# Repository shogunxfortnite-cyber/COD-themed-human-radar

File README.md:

# COD-themed-human-radar

## What is it
So basically its a,

radar with a LD2410C which can detect humans from a 6m range even when they are still, as the module also detects micromovements.

It also has a 2.8 inch TFT for displaying the fancy ui for the COD themed radar.

Its equipped with a ESP32 S3 DEVKIT C1 N16R8 for delivering fast and powerful performance.

## BOM

| Item | Qty | Supplier | Cost/item | Total Cost | Link |
| :--- | :---: | :--- | :---: | :---: | :--- |
| ESP32 S3 | 1 | Robocraze | $10.00 | $10.00 | [Link](https://robocraze.com/products/7semi-esp32-s3-dev-boardc-1-n8r8-wifi-bluetooth-dual-usb-c-rgb-led?variant=48519036272864) |
| 2.8 inch TFT | 1 | Robu | $7.00 | $7.00 | [Link](https://robu.in/product/2-8-inch-tft-lcd-non-touch-display-modulesd-card-support/) |
| The LD2410C | 1 | Robu | $7.00 | $7.00 | [Link](https://robu.in/product/hi-link-hlk-ld2410c-p-smd22x16mm-sensor-modules-rohs/) |
| The enclosure CAD | 1 | Robu | $4.00 | $4.00 | [Link](https://robu.in/product/3d-printing-service1/) |
| The PCB | 5 | Robu | $1.80 | $9.00 | [Link](https://robu.in/product/online-pcb-manufacturing-service/) |
| CAD lid | 1 | Robu | $2.00 | $2.00 | [Link](https://robu.in/product/3d-printing-service1/) |
| Estimated total shipping | 1 | - | $4.00 | $4.00 | - |
| **Total** | **11** | | | **$43.00** | |

# Guide
###### This course will guide you for making the PROJECT.

## Kicad

### Schematic 
So the schematic looks like this:

You can do the connections according to this.
#### Symbols and footprints 
For the symbols and footprints you can check out the folder named Symbols and footprints (It has already been made its just a copy), execept for esp 32, it can be natively downloaded from kicad itself.

### Footprint assignment

So you can assign the footprints according to  this image:

### PCB
So the initial start is like this:

Now we need to arrange it in a user friendly manner, so either you can arrange it like this or any other way which suites you:

Now comes the easy part, drawing the pcb outlines, this we would need to switch our current layer to edge.cuts and draw our custom outline.

I drew it like this:

Now comes the fun part routing, this has no restrictions, you can route it any way you want.

I have routed it like this:

For the red traces switch to F.cu layer and press X on your keyboard and for blue switch to B.cu.

Now comes the really fun part drawings, you can customize your board drawings your way.

Like this:

For the drawing part you would need to switch over to F.silkscreen.

### CAD 

For this part you have no restrictions, you can use any modelling software like freeCAD or tinkercad.

For making things easier you can import the radar.step and build the enclosure on top of it.

I made mine like this:

The Body:

The lid:

### Code 

For the code we would be using Arduino ide.

We can simply just copy and paste the code into arduino ide, set the board to esp32 s3 dev module and upload.

### final 3d view for PCB

## Problems I faced

I mainly faced problems in the CAD part as it was my first time designing an  enclosure for a PCB. The main problem was lifting the pcb up from the cad, so that the soldered pins dont clash with the CAD. It took me a time to figure it out but then I succeeded. With that I learnt how to design an enclosure in CAD.

# Built for half life

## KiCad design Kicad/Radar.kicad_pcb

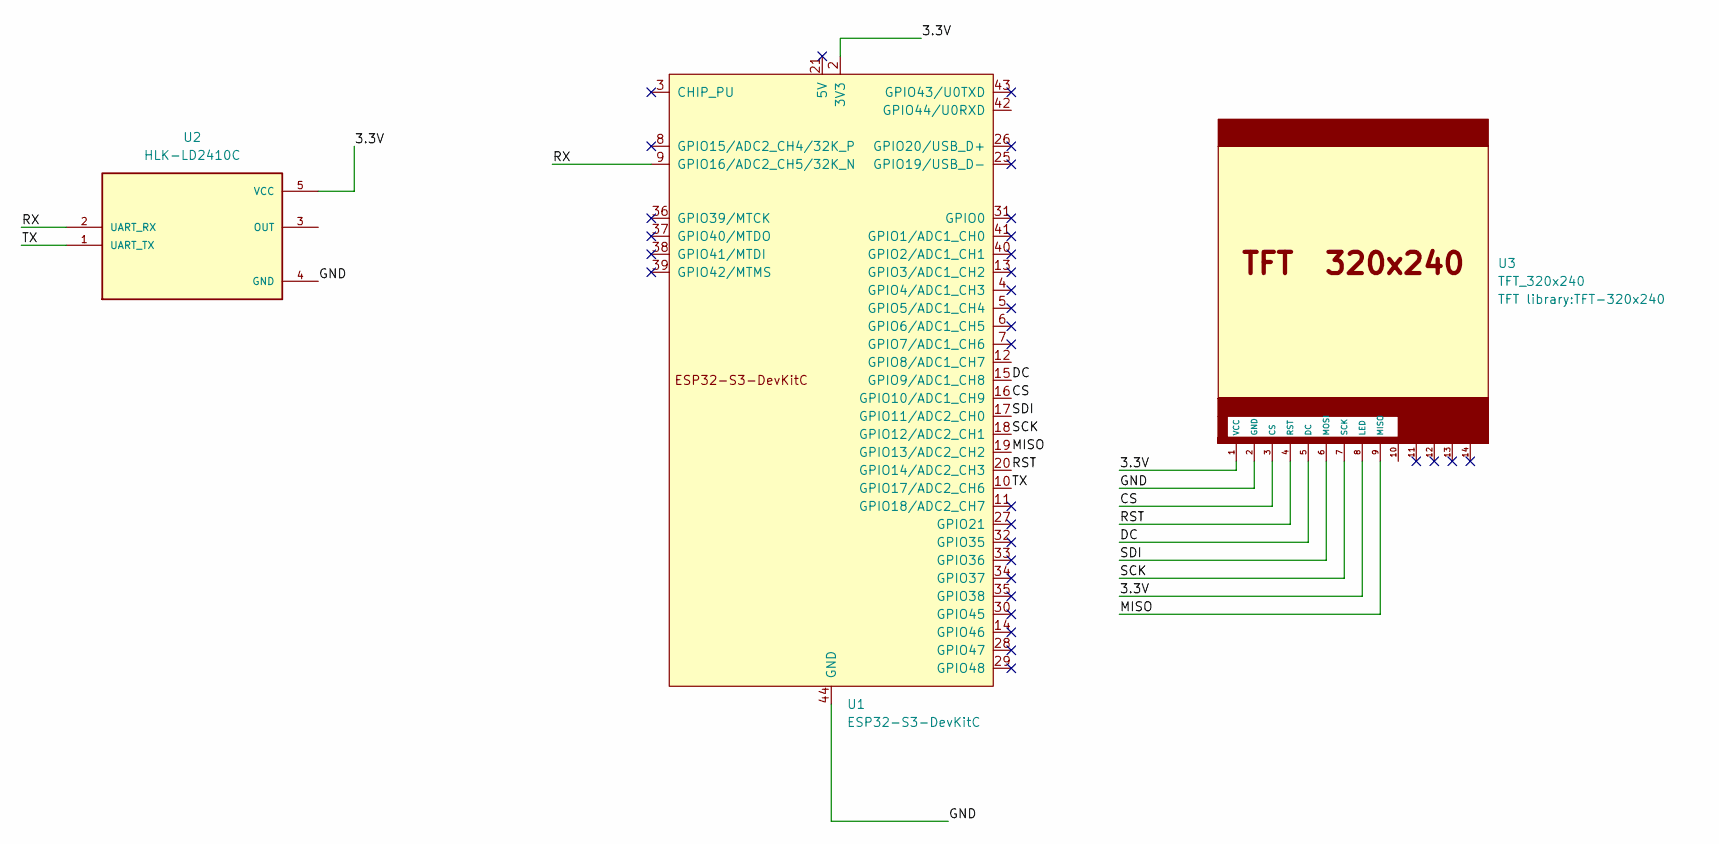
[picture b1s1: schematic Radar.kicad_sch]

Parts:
U1: ESP32-S3-DevKitC
U2: HLK-LD2410C; MODULE_HLK-LD2410C; PARTREV V1.00
U3: TFT_320x240; TFT-320x240

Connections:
/3.3V: U1.1 (3V3), U1.2 (3V3), U2.5 (VCC), U3.1 (VCC), U3.8 (LED)
/CS: U1.16 (GPIO10/ADC1_CH9), U3.3 (CS)
/DC: U1.15 (GPIO9/ADC1_CH8), U3.5 (DC)
/GND: U1.22 (GND), U1.23 (GND), U1.24 (GND), U1.44 (GND), U2.4 (GND), U3.2 (GND)
/MISO: U1.19 (GPIO13/ADC2_CH2), U3.9 (MISO)
/RST: U1.20 (GPIO14/ADC2_CH3), U3.4 (RST)
/RX: U1.9 (GPIO16/ADC2_CH5/32K_N), U2.2 (UART_RX)
/SCK: U1.18 (GPIO12/ADC2_CH1), U3.7 (SCK)
/SDI: U1.17 (GPIO11/ADC2_CH0), U3.6 (MOSI)
/TX: U1.10 (GPIO17/ADC2_CH6), U2.1 (UART_TX)

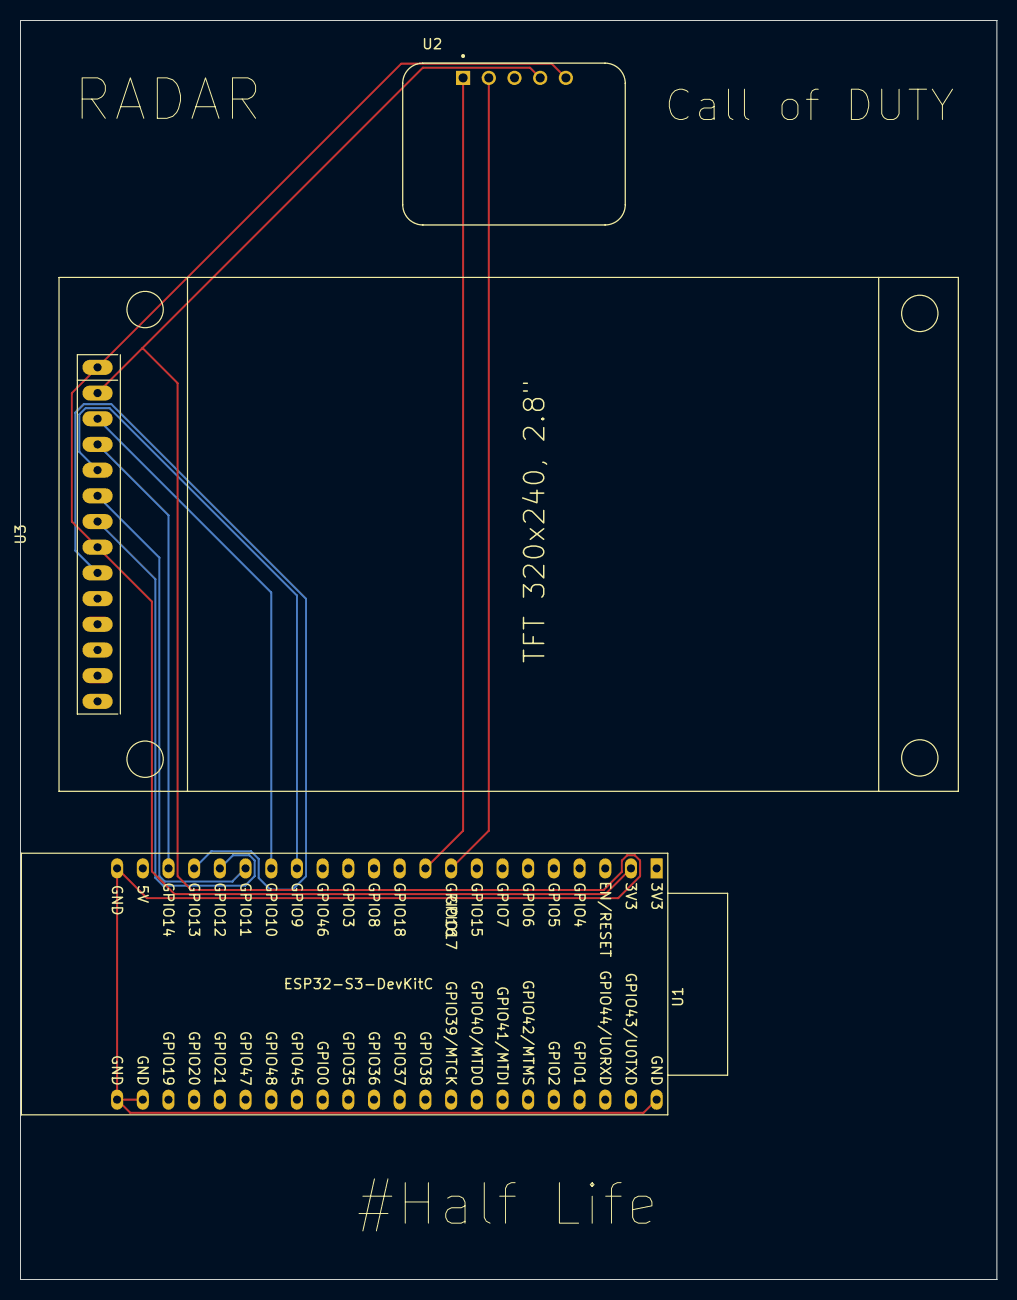
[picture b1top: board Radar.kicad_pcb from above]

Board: 2 copper layers, 96.5 x 124.5 mm, 3 parts (0 on the bottom side), 10 nets.
